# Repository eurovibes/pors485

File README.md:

<!-- SPDX-FileCopyrightText: 2025 Benedikt Spranger <b.spranger@linutronix.de> -->
<!-- SPDX-License-Identifier: CERN-OHL-S-2.0 -->

# pors485 - A Power over RS485 board

To pass electric power along with data on shared line is a common requirement.
The Power over RS485 board provides a solution to fit these needs. The board
can both inject and receive power from the bus. It is designed to operate with
Voltages from 7V to 36V up to a current of 4A.

## License rules

pors485 is provided under the terms of the CERN-OHL-S license version 2 as
provided in the LICENSES/CERN-OHL-S-2.0 file.

Instead of adding license boilerplates to the individual files, pors485 uses
SPDX license identifiers, which are machine parseable and considered legaly
equivalent.

The SPDX license identifier in pors485 shall be added at the first possible
line in a file which can contain a comment. This is normally the first line
except for scripts. Scripts require the #!PATH_TO_INTERPRETER tag in the
first line; place the SPDX identifier into the second line.

The SPDX license identifier is added in form of a comment.

## Copyright and License

Copyright Benedikt Spranger 2021.
This source describes Open Hardware and is licensed under the CERNOHL-S v2.
You may redistribute and modify this source and make products using it
under the terms of the CERN-OHL-S v2
(https://ohwr.org/cern ohl s v2.txt ).
This source is distributed WITHOUT ANY EXPRESS OR IMPLIED
WARRANTY, INCLUDING OF MERCHANTABILITY, SATISFACTORY
QUALITY AND FITNESS FOR A PARTICULAR PURPOSE. Please see
the CERN-OHL-S v2 for applicable conditions.
Source location: https://github.com/eurovibes/pors485
As per CERN-OHL-S v2 section 4, should You produce hardware based
on this source, You must where practicable maintain the Source Location
visible on the external case of the pors485 or other products you make using
this source.

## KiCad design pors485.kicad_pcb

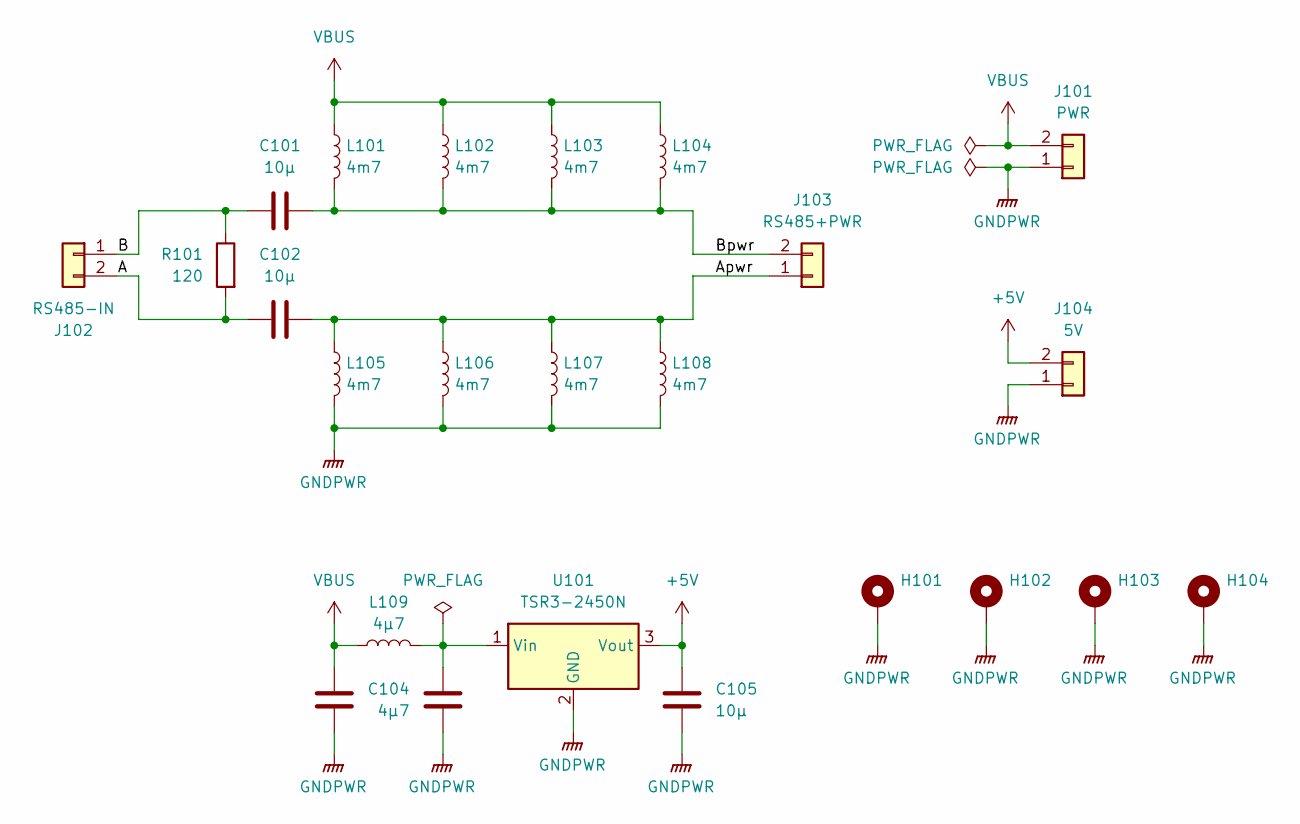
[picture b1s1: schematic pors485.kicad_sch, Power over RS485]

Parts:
C101, C102, C105: 10µ; C_0805_2012Metric; lcsc# C440198
C103, C104: 4µ7; C_1206_3216Metric; lcsc# C29823
H101, H102, H103, H104: MountingHole_3.2mm_M3_ISO14580_Pad
J101: PWR; TerminalBlock_WAGO_236-402_1x02_P5.00mm_45Degree
J102: RS485-IN; TerminalBlock_WAGO_236-402_1x02_P5.00mm_45Degree
J103: RS485+PWR; TerminalBlock_WAGO_236-402_1x02_P5.00mm_45Degree
J104: 5V; TerminalBlock_WAGO_236-402_1x02_P5.00mm_45Degree
L101, L102, L103, L104, L105, L106, L107, L108: 4m7; L_15x15mm_H8mm; lcsc# C970556
L109: 4µ7; L_Changjiang_FXL0530; lcsc# C177246
R101: 120; R_1206_3216Metric; lcsc# C17909
U101: TSR3-2450N; Converter_DCDC_TRACO_TSR2-24xxN_TSR2-24xxxN_THT

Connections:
+5V: C105.2, J104.2, U101.3 (Vout)
/A: C102.1, J102.2, R101.2
/Apwr: C102.2, J103.1, L105.1, L106.1, L107.1, L108.1
/B: C101.1, J102.1, R101.1
/Bpwr: C101.2, J103.2, L101.2, L102.2, L103.2, L104.2
GNDPWR: C103.2, C104.2, C105.1, H101.1, H102.1, H103.1, H104.1, J101.1, J104.1, L105.2, L106.2, L107.2, L108.2, U101.2 (GND)
unnamed: C104.1, L109.2, U101.1 (Vin)
VBUS: C103.1, J101.2, L101.1, L102.1, L103.1, L104.1, L109.1

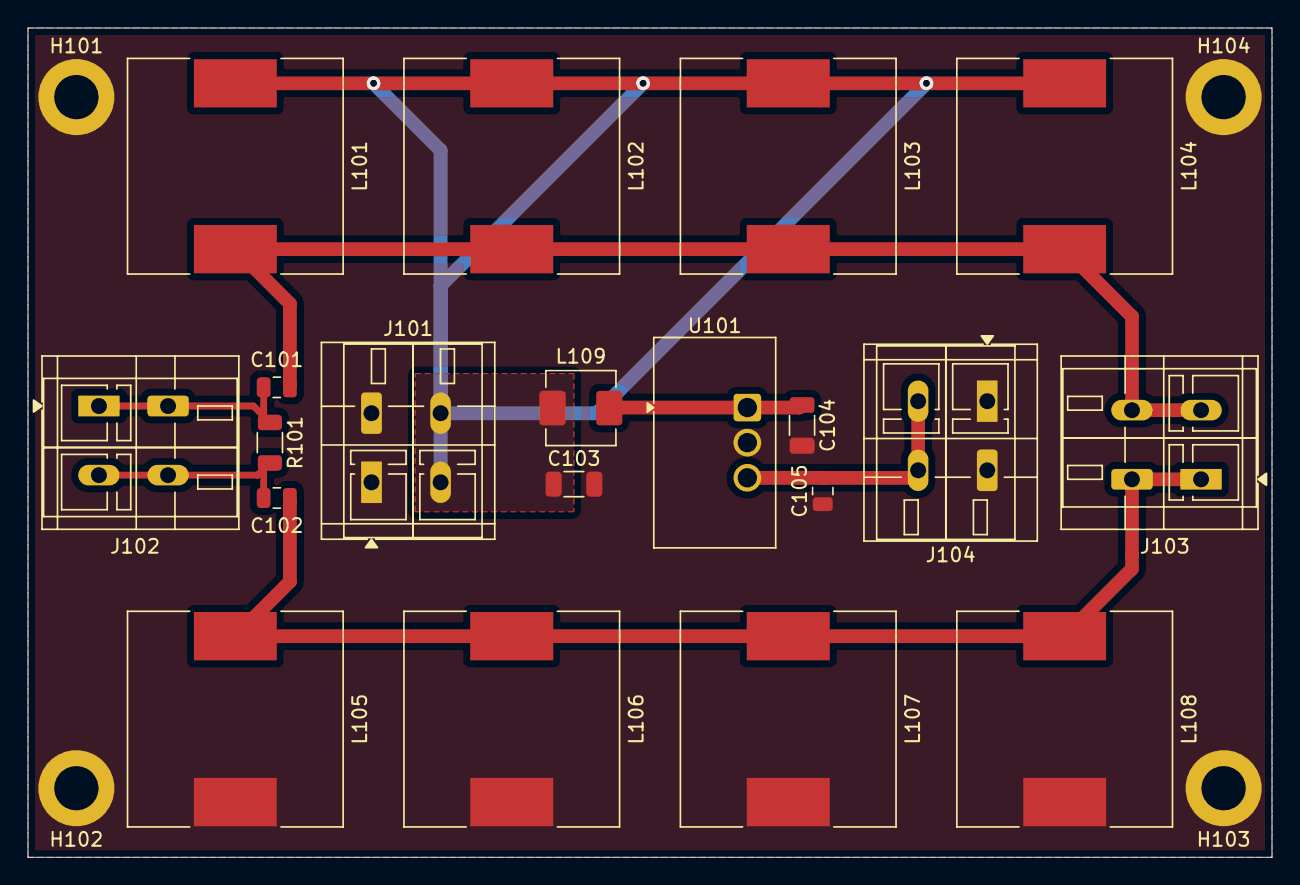
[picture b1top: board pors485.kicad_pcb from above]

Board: 2 copper layers, 90.0 x 60.0 mm, 24 parts (0 on the bottom side), 8 nets.

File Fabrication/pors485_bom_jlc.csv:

"Comment","Designator","Footprint","LCSC Part #"
"4µ7","C103,C104","C_1206_3216Metric","C29823"
"10µ","C101,C102,C105","C_0805_2012Metric","C440198"
"4µ7","L109","L_Changjiang_FXL0530","C177246"
"4m7","L101,L102,L103,L104,L105,L106,L107,L108","L_15x15mm_H8mm","C970556"
"120","R101","R_1206_3216Metric","C17909"

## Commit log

2025-12-02 Initial
2025-12-02 Add logo
2025-12-02 Add github CI/CD action
2025-12-02 Deploying to gh-pages from @ eurovibes/pors485@f551cda937f235917630c55d7a5e2ef737866fe8 🚀
2025-12-02 Deploying to gh-pages from @ eurovibes/pors485@853ceb91ec45b5514aa7765d0c1fb7f60e517a3a 🚀
2025-12-02 Deploying to gh-pages from @ eurovibes/pors485@1cf3faf7323da217d3328c908e8c2efa7589ea1e 🚀
2025-12-02 Initial gh-pages commit

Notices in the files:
pors485.kicad_pcb:
This work is licensed under the CERN-OHL-S v2
